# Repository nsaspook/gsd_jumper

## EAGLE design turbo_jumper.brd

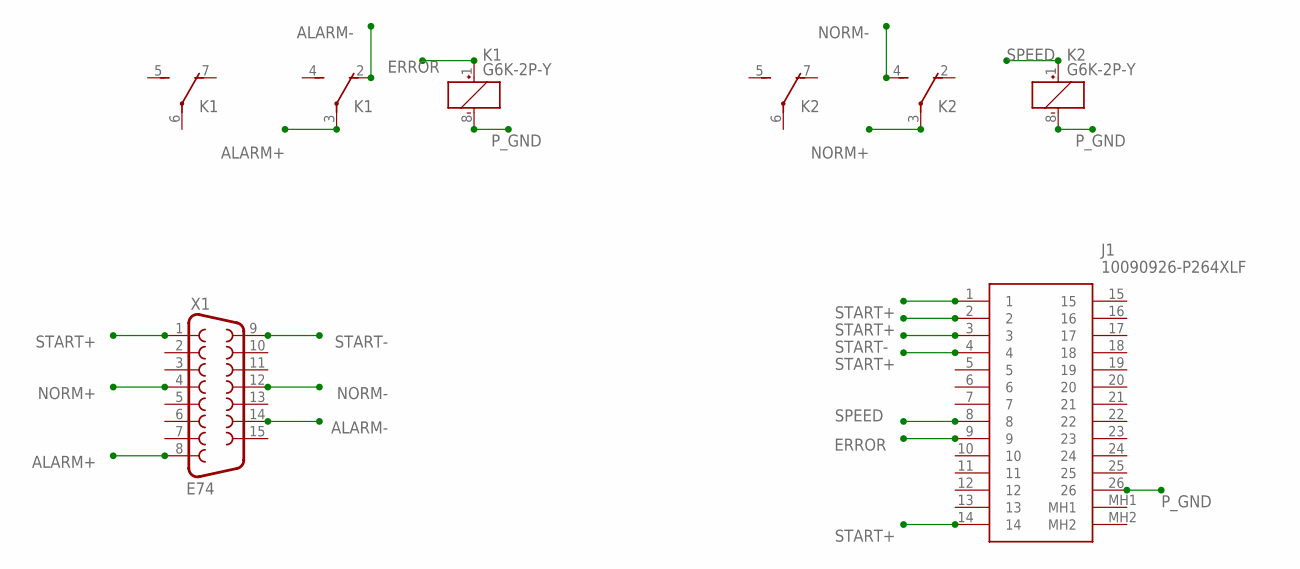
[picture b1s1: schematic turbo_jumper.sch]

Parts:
J1: 10090926-P264XLF; 10090926P264XLF
K1, K2: G6K-2P-Y
X1: E74; F15VP

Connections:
ALARM+: K1.3, X1.8
ALARM-: K1.2 (O), X1.14
ERROR: J1.9, K1.1 (+)
NORM+: K2.3, X1.4
NORM-: K2.4 (S), X1.12
P_GND: J1.26, K1.8 (-), K2.8 (-)
SPEED: J1.8, K2.1 (+)
START+: J1.1, J1.2, J1.4, J1.14, X1.1
START-: J1.3, X1.9

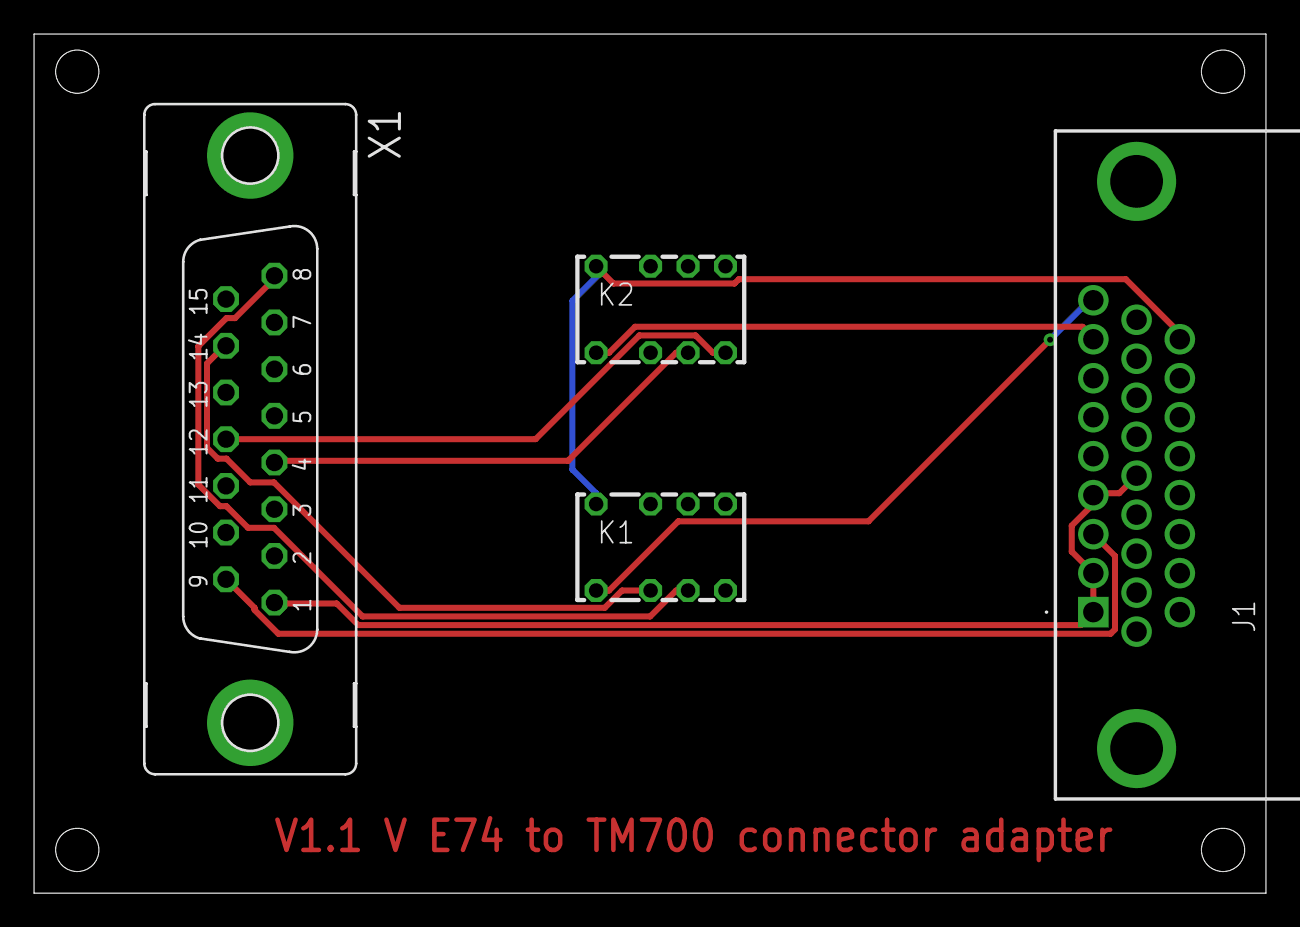
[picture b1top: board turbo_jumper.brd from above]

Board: 2 copper layers, 72.4 x 50.5 mm, 4 parts (0 on the bottom side), 9 nets.
